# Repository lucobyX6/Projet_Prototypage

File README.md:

# Projet_Prototypage
Projet de prototypage avec électrode capacitive - 1A - PICHOT Thomas | VINCENT Lucas

TO DO LIST : 

0. Décrire le fonctionnement du système
1. Concevoir le Pinout
2. Concevoir le PCB
3. Réaliser le montage virtuellement
4. Réaliser le montage expérimental <--
5. Concevoir le support plastique
6. Imprimer le support plastique
7. Réaliser le Code
8. Tester l'ensemble
9. Écrire le rapport

Date de rendu : 5 juin

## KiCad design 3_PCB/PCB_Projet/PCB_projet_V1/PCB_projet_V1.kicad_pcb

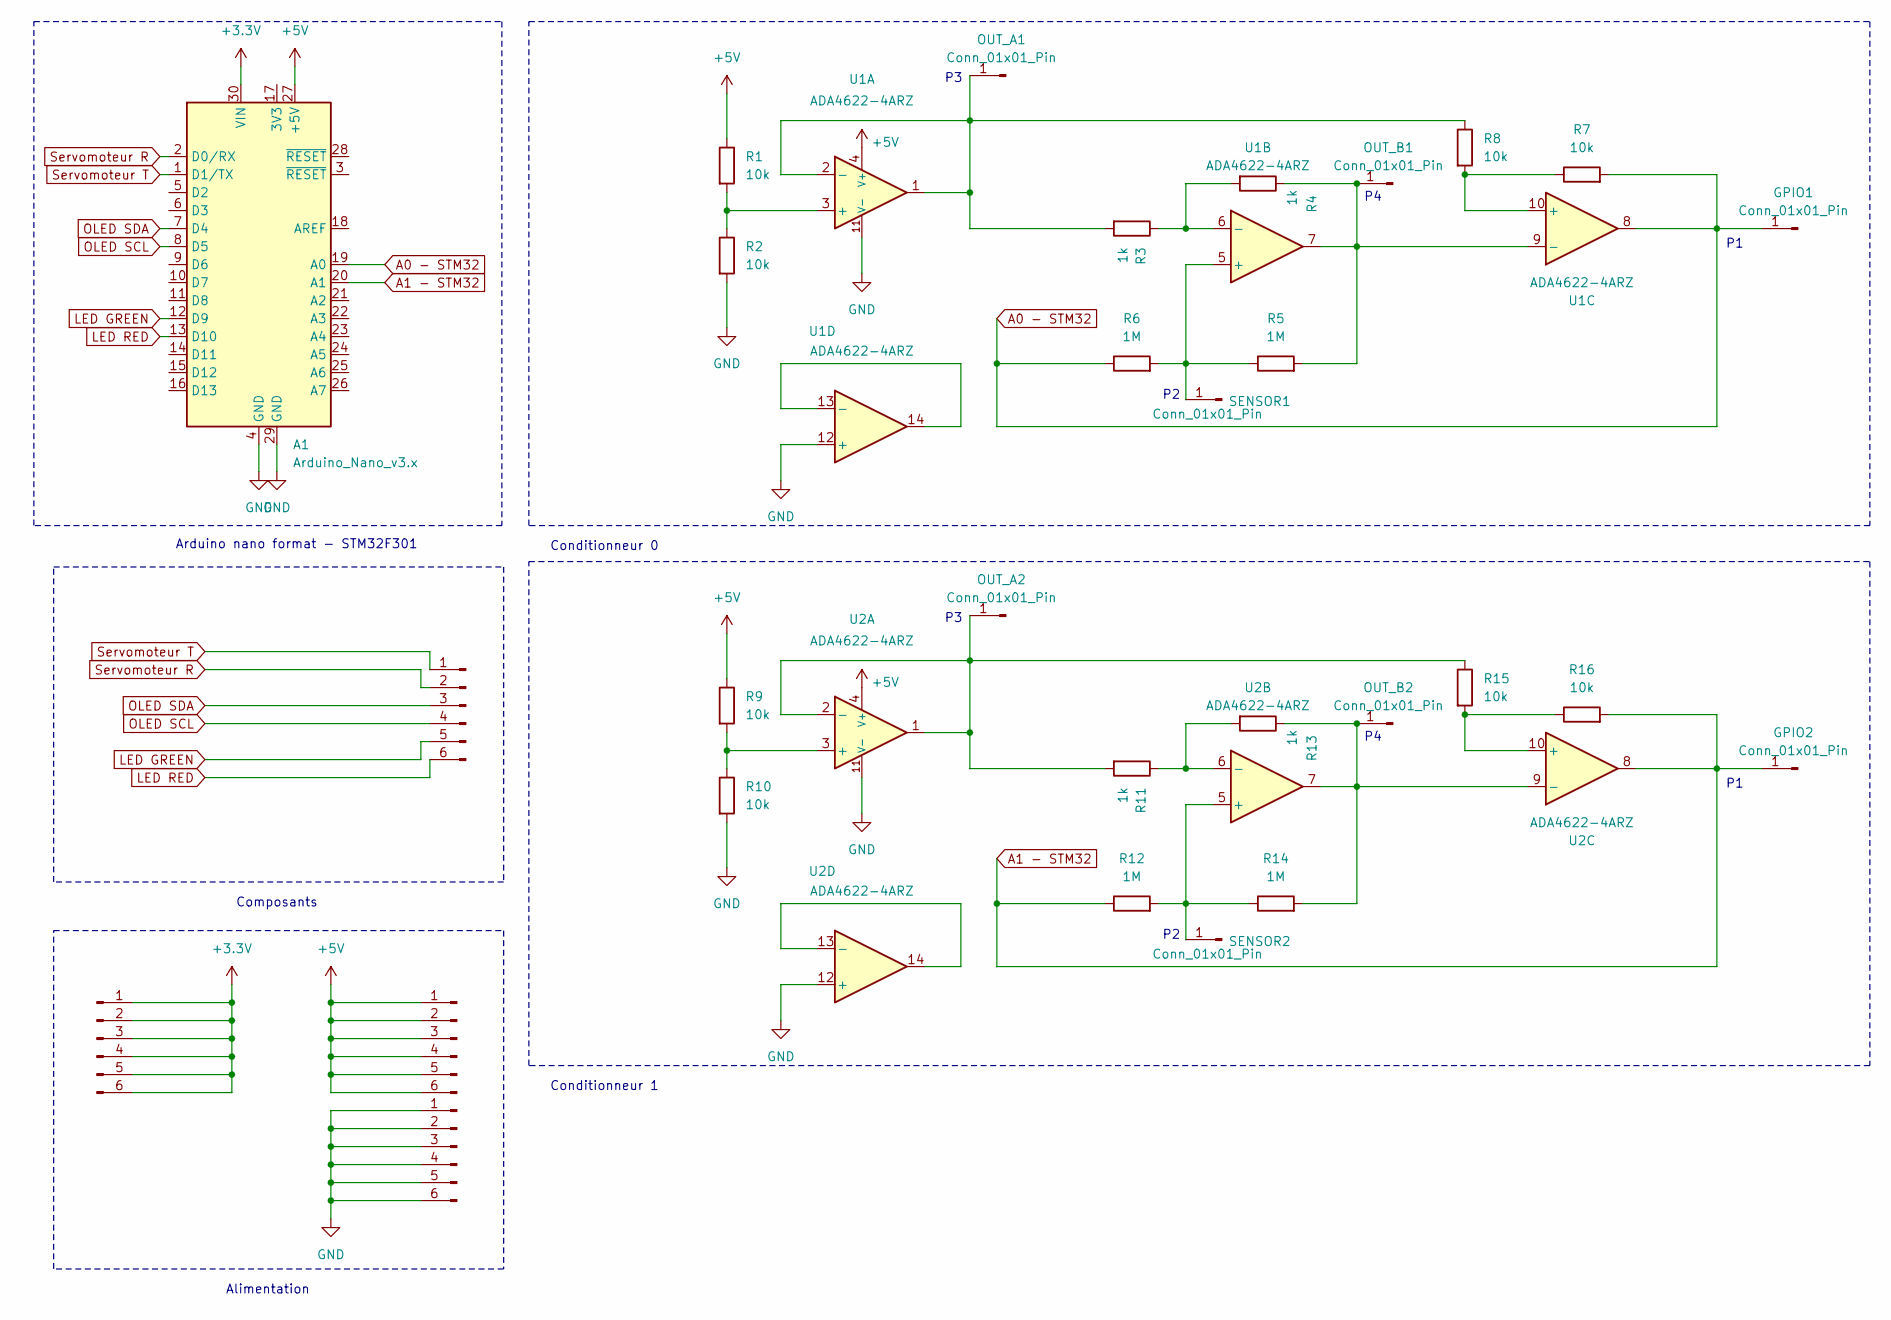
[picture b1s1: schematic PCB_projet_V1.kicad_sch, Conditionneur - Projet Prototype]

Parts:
A1: Arduino_Nano_v3.x; Arduino_Nano
GPIO1, GPIO2: Conn_01x01_Pin; PinHeader_1x01_P2.54mm_Vertical
J1, J2, J3, J4: Conn_01x06_Pin; PinHeader_1x06_P2.54mm_Vertical
OUT_A1, OUT_A2: Conn_01x01_Pin; PinHeader_1x01_P2.54mm_Vertical
OUT_B1, OUT_B2: Conn_01x01_Pin; PinHeader_1x01_P2.54mm_Vertical
R1, R2, R7, R8, R9, R10, R15, R16: 10k; R_0805_2012Metric
R3, R4, R11, R13: 1k; R_0805_2012Metric
R5, R6, R12, R14: 1M; R_0805_2012Metric
SENSOR1, SENSOR2: Conn_01x01_Pin; PinHeader_1x01_P2.54mm_Vertical
U1, U2: ADA4622-4ARZ; SOIC-14_3.9x8.7mm_P1.27mm

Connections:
+3.3V: A1.30 (VIN), J4.1, J4.2, J4.3, J4.4, J4.5, J4.6
+5V: A1.27 (+5V), J2.1, J2.2, J2.3, J2.4, J2.5, J2.6, R1.1, R9.1, U1.4 (V+), U2.4 (V+)
A0 - STM32: A1.19 (A0), GPIO1.1, R6.1, R7.2, U1.8
A1 - STM32: A1.20 (A1), GPIO2.1, R12.1, R16.2, U2.8
GND: A1.4 (GND), A1.29 (GND), J3.1, J3.2, J3.3, J3.4, J3.5, J3.6, R2.2, R10.2, U1.11 (V-), U1.12 (+), U2.11 (V-), U2.12 (+)
LED GREEN: A1.12 (D9), J1.5
LED RED: A1.13 (D10), J1.6
unnamed: OUT_A1.1, R3.2, R8.1, U1.1, U1.2 (-)
unnamed: OUT_A2.1, R11.2, R15.1, U2.1, U2.2 (-)
unnamed: OUT_B1.1, R4.1, R5.2, U1.7, U1.9 (-)
unnamed: OUT_B2.1, R13.1, R14.2, U2.7, U2.9 (-)
unnamed: R5.1, R6.2, SENSOR1.1, U1.5 (+)
unnamed: R12.2, R14.1, SENSOR2.1, U2.5 (+)
unnamed: R1.2, R2.1, U1.3 (+)
unnamed: R3.1, R4.2, U1.6 (-)
unnamed: R7.1, R8.2, U1.10 (+)
unnamed: U1.13 (-), U1.14
unnamed: R9.2, R10.1, U2.3 (+)
unnamed: R11.1, R13.2, U2.6 (-)
unnamed: R15.2, R16.1, U2.10 (+)
unnamed: U2.13 (-), U2.14
OLED SCL: A1.8 (D5), J1.4
OLED SDA: A1.7 (D4), J1.3
Servomoteur R: A1.2 (D0/RX), J1.2
Servomoteur T: A1.1 (D1/TX), J1.1

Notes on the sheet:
Conditionneur 0
Composants
Conditionneur 1
Arduino nano format - STM32F301
Alimentation

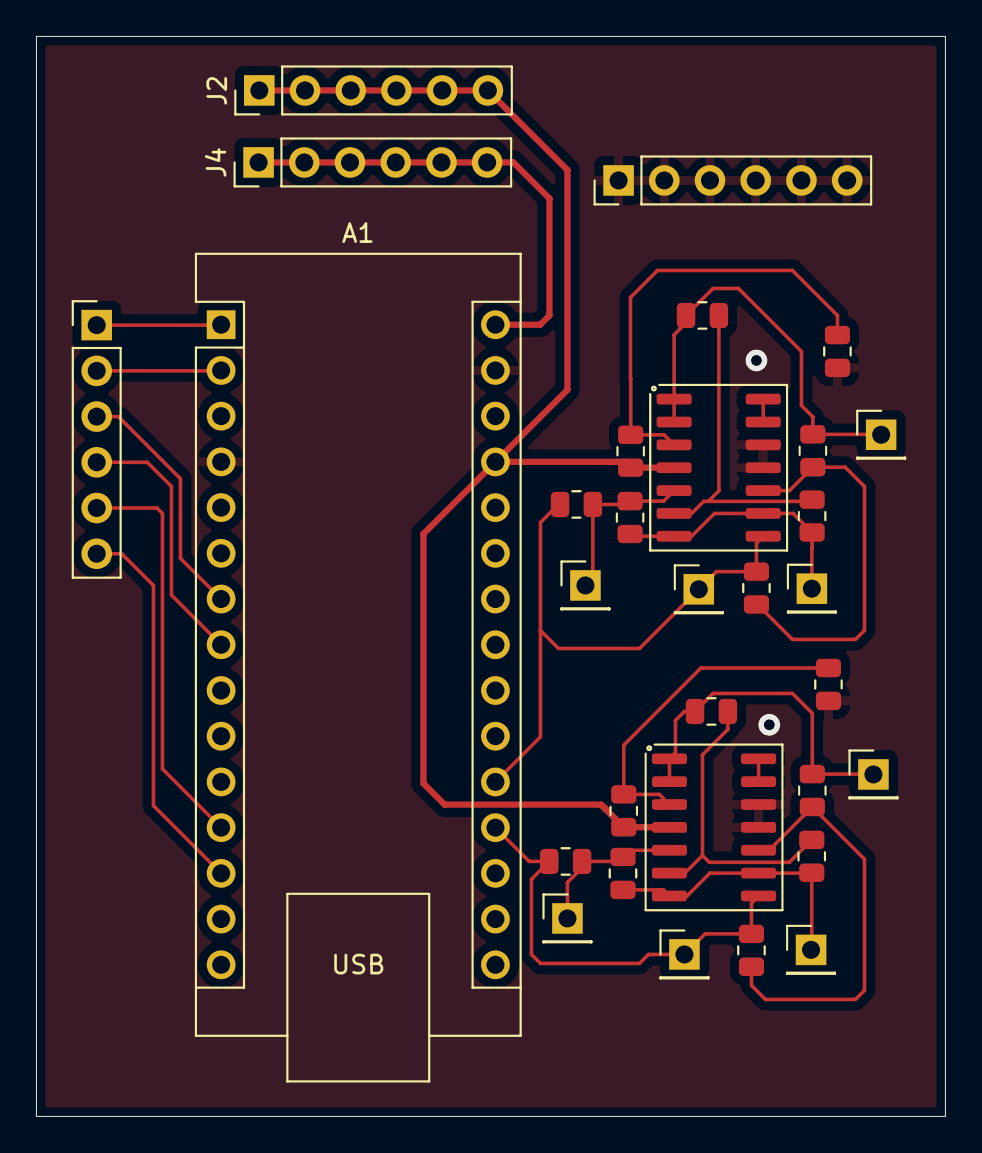
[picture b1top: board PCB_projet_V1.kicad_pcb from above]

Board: 2 copper layers, 50.5 x 60.0 mm, 31 parts (0 on the bottom side), 25 nets.

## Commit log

2024-05-15 Init
2024-05-15 j'ai modifié le readme parce qu'il était nul
2024-05-15 Création du code STM32
2024-05-15 Transmission + calculs
2024-05-15 Correction problème de communication
2024-05-16 Problème F et C
2024-05-16 Code fonctionnel
2024-05-16 To do list du projet
2024-05-16 Mise à jour du README - TO DO
2024-05-20 Conditionneur 2 entrées
2024-05-21 Pinout init
2024-05-21 pinout init 2
2024-05-21 stade 1
2024-05-22 Liste des PINOUT à remplir
2024-05-22 TO DO LIST 2
2024-05-22 A remplir
2024-05-22 PINOUT
2024-05-22 Concevoir le PCB
2024-05-22 PCB 1
2024-05-22 PCB erreurs
2024-05-22 new 2
2024-05-22 Fin pinout
2024-06-05 PCB Electrode
2024-06-05 Modèle 3D
